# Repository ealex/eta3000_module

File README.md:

# eta3000_module
2S balancer module based on the ETA3000 inductive balancer IC

This uses the SOT23-6 chip and it's designed for the smallest footprint possible.
The ballancing curent is intended to be low, for heat dissipation reasons.
The modules are intented to be conected toghether for more than 2S packs.

TODO: update README when the PCB's are here

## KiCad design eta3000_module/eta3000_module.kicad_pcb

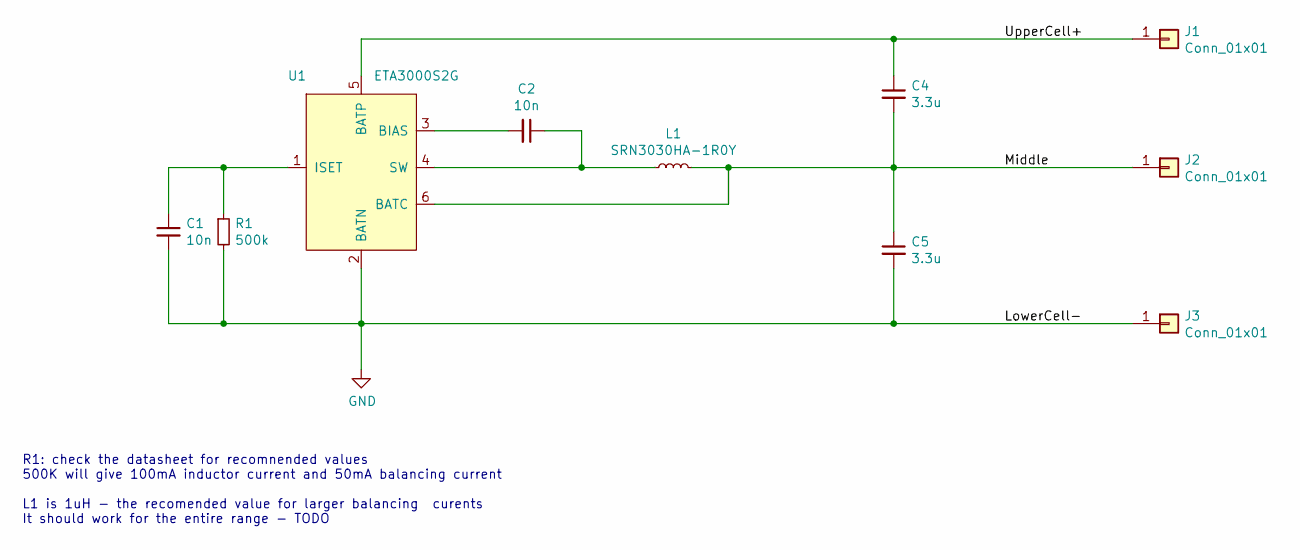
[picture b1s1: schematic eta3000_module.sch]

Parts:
C1, C2: 10n; C_0805_2012Metric
C4, C5: 3.3u; C_0805_2012Metric
J1, J2, J3: Conn_01x01; PinSocket_1x01_P2.54mm_Vertical
L1: SRN3030HA-1R0Y; SRN3030
R1: 500k; R_0805_2012Metric
U1: ETA3000S2G; SOT-23-6

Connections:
/Middle: C4.2, C5.1, J2.1, L1.2, U1.6 (BATC)
/UpperCell+: C4.1, J1.1, U1.5 (BATP)
GND: C1.2, C5.2, J3.1, R1.2, U1.2 (BATN)
unnamed: C1.1, R1.1, U1.1 (ISET)
unnamed: C2.1, L1.1, U1.4 (SW)
unnamed: C2.2, U1.3 (BIAS)

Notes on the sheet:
R1: check the datasheet for recomnended values 500K will give 100mA inductor current and 50mA balancing current L1 is 1uH - the recomended value for larger balancing curents It should work for the entire range - TODO

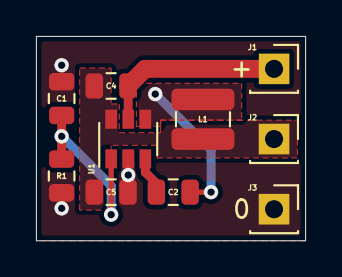
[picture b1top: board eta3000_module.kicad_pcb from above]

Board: 2 copper layers, 15.0 x 11.3 mm, 10 parts (0 on the bottom side), 6 nets.

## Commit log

2022-08-29 add component documentation
2022-08-29 schematic and gerber files
2022-09-01 add BOM
